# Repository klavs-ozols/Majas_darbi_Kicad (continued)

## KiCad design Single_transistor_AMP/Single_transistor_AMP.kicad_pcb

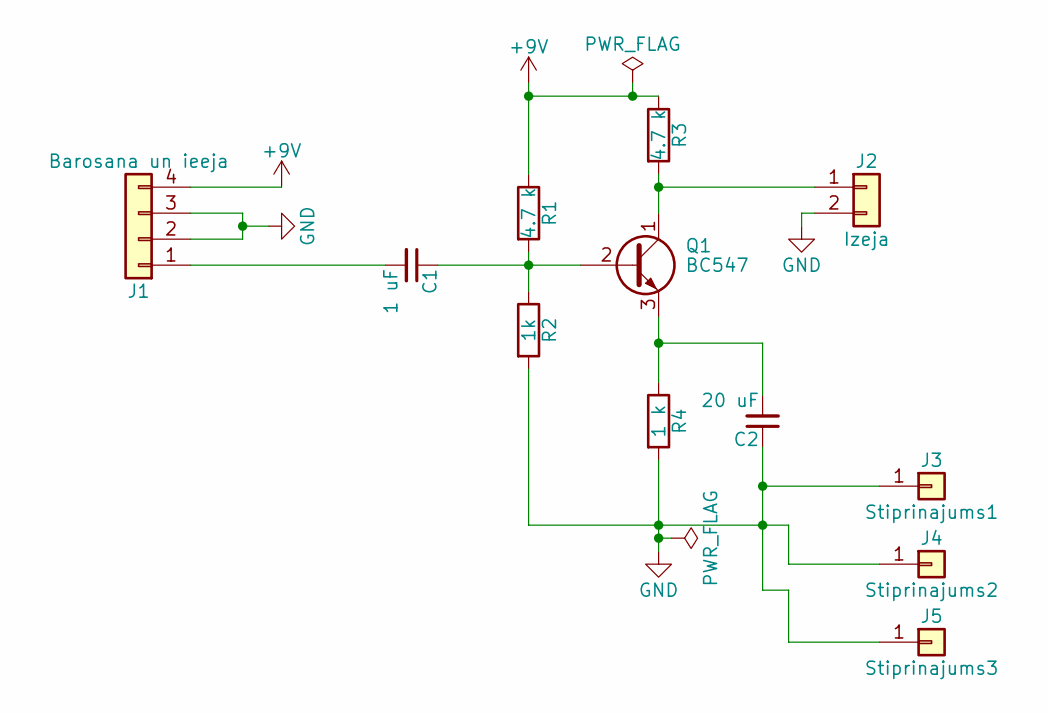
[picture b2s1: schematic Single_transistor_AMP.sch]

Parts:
C1: 1 uF; C_Rect_L10.0mm_W2.5mm_P7.50mm_MKS4
C2: 20 uF; C_Rect_L10.0mm_W2.5mm_P7.50mm_MKS4
J1: Barosana un ieeja; AK300-4
J2: Izeja; AK300-2
J3: Stiprinajums1; MountingHole_2.2mm_M2_Pad
J4: Stiprinajums2; MountingHole_2.2mm_M2_Pad
J5: Stiprinajums3; MountingHole_2.2mm_M2_Pad
Q1: BC547; TO-92_Molded_Narrow
R1, R3: 4.7 k; R_Axial_DIN0204_L3.6mm_D1.6mm_P7.62mm_Horizontal
R2: 1k; R_Axial_DIN0207_L6.3mm_D2.5mm_P10.16mm_Horizontal
R4: 1 k; R_Axial_DIN0207_L6.3mm_D2.5mm_P10.16mm_Horizontal

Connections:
+9V: J1.4, R1.1, R3.1
GND: C2.1, J1.2, J1.3, J2.2, J3.1, J4.1, J5.1, R2.2, R4.2; also elsewhere on the board
unnamed: C1.1, Q1.2 (B), R1.2, R2.1
unnamed: C1.2, J1.1
unnamed: C2.2, Q1.3 (E), R4.1
unnamed: J2.1, Q1.1 (C), R3.2

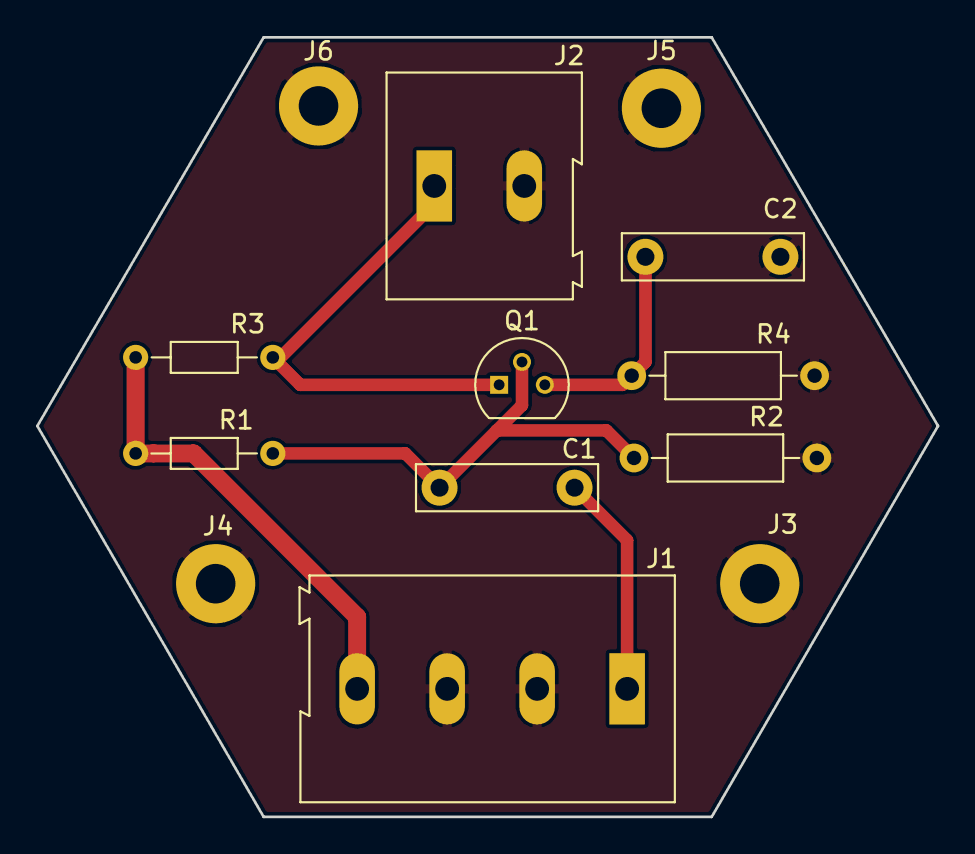
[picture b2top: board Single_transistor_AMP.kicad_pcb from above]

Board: 2 copper layers, 50.0 x 43.3 mm, 13 parts (0 on the bottom side), 6 nets.

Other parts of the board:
J6: Stiprinajums4; MountingHole_2.2mm_M2_Pad

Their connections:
GND: J6.1; also elsewhere on the board

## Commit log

2018-02-19 README update to test GitHub Repo
2018-03-13 Pievienots 1. majasdarbs
2018-03-13 1. maajasdarbs ar bibliteeku
2018-03-14 Tika izlabota 1. majasdarba kluuda
2018-03-14 Tiek izlabota 1. majasdarba kluuda
2018-03-14 Shii ir izlabotaa 1. maajasdarba versija
2018-03-15 Izlaboju 1. MD kljuudu
2018-03-15 Shis ir iesniegtais stundaa izpildiitas darbs ar viena transistora pastiprinaataaju.
2018-03-21 Shis ir 2. majasdarbs(MD2), kur bija jaizveido "Power Supply" modelis.
2018-03-28 Shis ir 3. MD par bateriju tureetaajiem
2018-04-04 Shis ir iesniegts majasdarbs, kur jaaiestata plates iestatijumi
2018-04-24 Majasdarbs peec 8. lekcijas, kur jauzzimee plate
2018-04-26 Single_transistor_AMP 2. iteraacija
2018-04-26 Single transistor AMP 2. iteraacija
2018-05-02 MD pēc 10. lekcijas
2018-05-02 MD pec 10. lekcijas, 2 iteraacija
2018-05-02 MD peec 11. iteraacijas
2018-05-20 Shii ir 1. iteraacija Kursa darbam.
2018-05-26 Shii ir 2. iteraacija kursa darbam!
2018-05-30 Shii ir kursa darba 3. iteraacija
2018-05-30 Kursa darba plates 4. iteraacija
2018-05-30 Vai straadaa 4. iteraacija?
2018-05-31 Vai straadaa ?
2018-05-31 Vai tagad straadaa?
2018-06-09 Shiii ir 5. iteraacija manai platei - layouts
2018-06-10 Shis ir mans meeginaajums iztraseet plati ( nepabeigts- vajag paliidziibu)
2018-06-13 Kursa/Prakses darba pabeigtaa plates versija
2018-06-17 1. Prototipa finaala versija
